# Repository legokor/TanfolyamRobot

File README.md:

# LEGO Kör - TanfolyamRobot

## Fejlesztő környezet

Korábban az STMicroelectronics által biztosított `STM32CubeIDE`-t használtuk a firmware fejlesztéséhez, azonban ez egy elég nehézkes és lassú eszköz. Ezért a tanfolyam során áttérünk egy könnyebben használható és gyorsabb parancssoros toolchain-re, az `STM32CubeCLT`-re. Ezt a toolchain-t a Visual Studio Code nevű (továbbiakban `VSCode`) kód szerkesztővel fogjuk használni, így a teljes fejlesztés (fordítás, feltöltés) nagyon könnyen indítható lesz néhány előre beállított `task`-kal.

## Toolchain

Az előző fejezetben említett módon a firmware fejlesztéséhez az STMicroelectronics parancsoros eszközeit használjuk. Sajnos ezek letöltése regisztrációhoz kötött, ezért feltöltöttük a telepítő fájlokat [a körös drive-ra](https://drive.google.com/drive/folders/1nJ2nfvr9kbIkVAWmcgEXpbxK1OUlX8sQ?usp=sharing), így regisztráció nélkül is telepíteni tudjátok - persze teljesen megértjük, ha nem akartok random drive-os fájlokat telepíteni, viszont ez esetben muszáj regisztrálnotok az [STMicroelectronics weboldalán](https://www.st.com/en/development-tools/stm32cubeclt.html), és onnan letölteni.

Letöltés után a telepítő fájlt futtatva telepítsétek a `STM32CubeCLT`-t egy kényelmes helyre, például `C:\STM32CubeCLT`-be.

**FONTOS:** az `STM32CubeCLT` telepítése után újra kell indítani a `VSCode`-ot amennyiben az már meg volt nyitva, különben a `VSCode` nem fogja látni a telepített toolchain-t. Ezen felül Linux rendszerek esetében előfordulhat, hogy a gépet is újra kell indítani, hogy a megfelelő környezeti változók beálljanak.

Jelenleg Windows 10/11-en és Ubuntu-n teszteljük a szoftvert. Más (Linux alapú) platformokon is valószínűleg működni fog - de ezt nem tudjuk garantálni.

## Robot illesztőszoftver

A robotra a firmware letöltése virtuális soros porton történik, a roboton az USB csatlakozó egy `FT232RL` chiphez kapcsolódik.

Előfordulhat Windows esetében, hogy az nem telepíti automatikusan a virtuális soros port driverét. Erre az esetre a fentebbi drive linken elérhető Windows zip-ben találtok egy plusz driver telepítőt, de amúgy ezt is le tudjátok tölteni az [FTDI weboldaláról](https://ftdichip.com/wp-content/uploads/2021/08/CDM212364_Setup.zip), majd pedig kibontani és telepíteni.

## Kiinduló projekt letöltése, megnyitása

A kiinduló projektet a [GitHub repojából](https://github.com/legokor/TanfolyamRobot) tudjuk letölteni, ehhez az oldal megnyitása után jobb oldalt a `Releases` fül alatt kell kiválasztanunk a **legújabb kiadást**, majd a `tanfrobot.zip` fájlra kell kattintani.

A letöltött fájlt helyezzük el egy kényelmes helyre, például `Documents/Lego_Tanfolyam` mappába, majd bontsuk ki. A kibontás után nyissuk meg a `VSCode`-ot, és a `File -> Open Folder...` menüponttal nyissuk meg a kibontott `firmware` mappát (mely többek közt az `Application`, `Drivers`, `Tools` könyvtárakat tartalmazza).

*Extra tipp:* a `VSCode`-ban érdemes telepíteni az `ms-vscode.cpptools` nevű bővítményt, mely C/C++ nyelv támogatást ad a szerkesztőhöz, így például szintaxis kiemelést és automatikus kiegészítést biztosít.

--------------------------------------------

--------------------------------------------

## *Csak a tanfolyamon kell:* projekt áttekintése, build és upload

Az imént megnyitott projektünk fájljait az IDE bal oldalán láthatjuk. A kód számunkra lényegi része a `tanfolyamrobot/Application/src/app.c` fájl lesz. Itt kell majd megoldanunk a tanfolyam során a feladatokat. Az itt található `app_main()` függvény gombnyomásra indul. Ha ebből a függvényből visszatér a programunk, akkor a robot leáll és a kijelzőn megjeleníti a visszatérési értéket.

A kód fordításához és a robotra való feltöltéséhez a `VSCode`-ban előre beállítottunk néhány `task`-ot, melyeket a `CTRL+SHIFT+B` billentyűkombinációval tudtok elindítani. E billentyűkombináció megnyomása után egy legördülő menüből választhatjátok ki, hogy mit szeretnétek csinálni - számunkra a `CMake Build` és az `STM32 Flash Firmware (FTDI)` lesz a fontos. Előbbi lefordítja a kódot, utóbbi pedig feltölti a robotra. A kiválasztás után egy újabb kérdés fog megjelenni, hogy melyik konfigurációt szeretnénk használni - válasszuk a `Release`-t, majd nyomjunk egy entert.

**FONTOS:** a `CMake Build`-et mindig futtassátok le a `STM32 Flash Firmware (FTDI)` előtt, különben a régi kód fog futni a roboton, nem pedig a legutóbb módosított verzió.

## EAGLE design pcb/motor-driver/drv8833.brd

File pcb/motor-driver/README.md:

# DRV8833 module

This is a carrier board for the DRV8833 dual H-bridge motor driver chip. It is a drop-in replacement for the cheap chinese 12 pin version.

Improvements:
 * Current sense resistors for the chip's current limiter feature
 * More capacitance on the power rail
 * Fault LED
 * Active-high fault output (still open-collector)

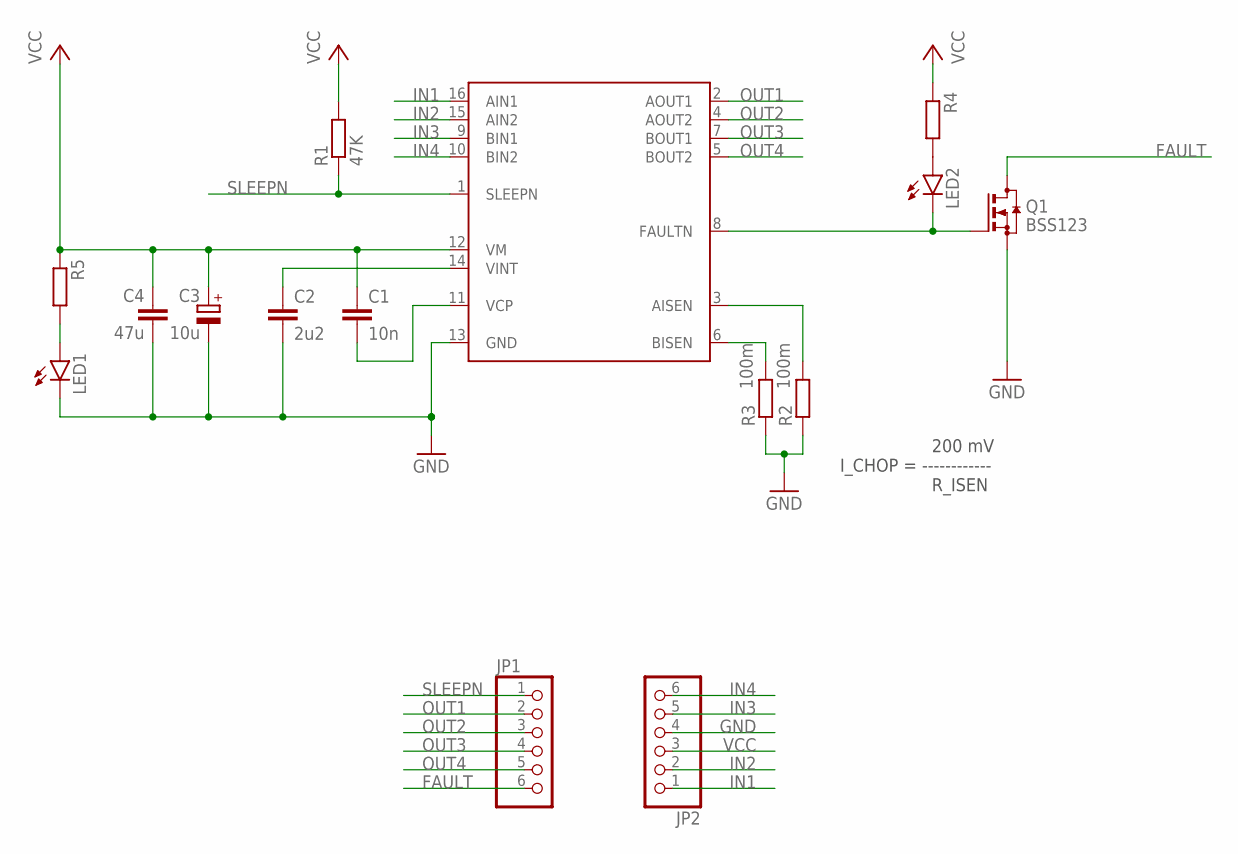
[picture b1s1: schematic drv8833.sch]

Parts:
C1: 10n; C0603
C2: 2u2; C0603
C3: 10u; A/3216-18W
C4: 47u; C1210
JP1, JP2: PINHD-1X6; 1X06
LED1, LED2: LEDCHIPLED_0805; CHIPLED_0805
Q1: BSS123; SOT23
R1: 47K; R0603
R2, R3: 100m; R1206
R4, R5: R0603
U$1: DRV8833; TSSOP-16

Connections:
AISEN: R2.2, U$1.3 (AISEN)
BISEN: R3.2, U$1.6 (BISEN)
FAULT: JP1.6, Q1.3 (D)
FAULTN: LED2.C, Q1.1 (G), U$1.8 (FAULTN)
FLT_AN: LED2.A, R4.2
GND: C2.2, C3.-, C4.2, JP2.4, LED1.C, Q1.2 (S), R2.1, R3.1, U$1.13 (GND)
IN1: JP2.1, U$1.16 (AIN1)
IN2: JP2.2, U$1.15 (AIN2)
IN3: JP2.5, U$1.9 (BIN1)
IN4: JP2.6, U$1.10 (BIN2)
OUT1: JP1.2, U$1.2 (AOUT1)
OUT2: JP1.3, U$1.4 (AOUT2)
OUT3: JP1.4, U$1.7 (BOUT1)
OUT4: JP1.5, U$1.5 (BOUT2)
PWR_LED: LED1.A, R5.2
SLEEPN: JP1.1, R1.1, U$1.1 (SLEEPN)
VCC: C1.1, C3.+, C4.1, JP2.3, R1.2, R4.1, R5.1, U$1.12 (VM)
VCP: C1.2, U$1.11 (VCP)
VINT: C2.1, U$1.14 (VINT)

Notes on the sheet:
200 mV I_CHOP = ------------ R_ISEN

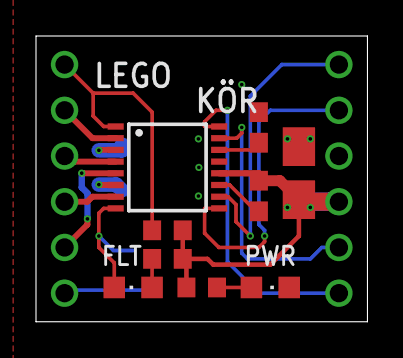
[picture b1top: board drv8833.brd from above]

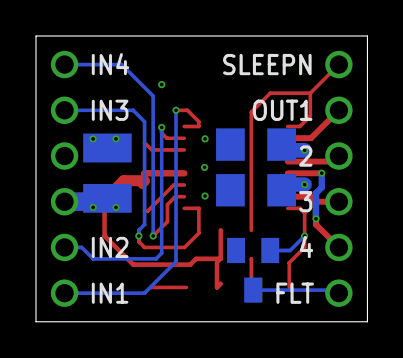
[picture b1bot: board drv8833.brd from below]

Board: 2 copper layers, 18.4 x 15.9 mm, 15 parts (6 on the bottom side), 19 nets.

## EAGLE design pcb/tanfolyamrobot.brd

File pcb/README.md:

# TanfolyamRobot - PCB design considerations

_Note: schematic net and pin names are formatted like_ `this`.

## Microcontroller

The main MCU is an [STM32F103C8T6](https://www.st.com/resource/en/datasheet/stm32f103c8.pdf) in LQFP64 package. There's an option to add an ESP8266 module which communicates with the main MCU via UART.

**The full STM32 pinout and pin assignments can be found in [STM32F103_pin_assignment.xls](STM32F103_pin_assignment.xls)**

### Programming

The STM32 can be programmed using the Serial Wire Debug interface or the integrated Device Firmware Updater. The F103's DFU only supports USART1, so that's connected to an FTDI FT232RL USB-UART converter.

In order to use the DFU, the MCU must be booted in System memory mode by pulling the `BOOT0` pin high at reset.
`BOOT0` is controlled by:
 * the FTDI chip's `RSTN` reset signal, which is high when USB is connected.
 * an FTDI output pin controlled by PC software. The pin can be selected by solder jumpers.

### Reset

Both controllers are connected to the same reset signal, which is a combination of the following reset sources:
 * The reset button
 * Debugger port
 * USB 5V connection
 * an FTDI output pin controlled by PC software. The pin can be selected by solder jumpers.

## Power supply

The battery input connects through a polarity protection MOSFET to the `VCC` rail, which drives the motors and the 5V regulator. Therefore the battery voltage must be at least 5V + the regulator's dropout voltage, and can be as high as the motors' and the motor driver's maximum operating voltage. The polarity protection MOSFET's absolute maximum V<sub>GS</sub> and V<sub>DS</sub> must be higher than the supply voltage.

The `+5V` rail powers the FTDI chip, LCD, ultrasonic sensor, motor encoders, and the servo motor. Therefore the ultrasonic sensor and motor encoder outputs shall be connected to a 5V tolerant MCU pin or level-shifted to 3.3V.

The `+3V3` rail powers the rest of the system: STM32, ESP, color sensor, and it's also the `VCCIO` supply of the FTDI chip.

## Motors

The two motors are driven by a DRV8833 module. For maximum flexibility all of its input ports shall be connected to PWM cabable MCU pins, preferably using the same timer. The driver indicates overcurrent/overheat faults on the `FAULTN` pin, and the whole module can be enabled/disabled by the `SLEEPN` pin.

The STM32's timers have a built-in encoder pulse counter module, which uses the CH1-CH2 channel pair. The motors' encoder pins therefore shall be connected to these timer channels.

The servo output has a 3 pin header with 5V supply and a PWM pin.

## Sensors, LCD

The TCS3200 color sensor has a frequency output. 2 config pins activate the RGB color filters, and 2 config pins set the output frequency scaling. The output pin should be connected to a timer of the MCU. The timer's frequency is not critical as the output full scale frequency can be configured between 12 and 600 kHz.

The generic ultrasonic sensor has a trigger and an echo pin. `ECHO` shall be connected to an interrupt-capable MCU pin.

The character LCD screen operates in 4 bit mode. In this configuration only the `D4`-`D7`, `EN` and `RST` pins are used. Contrast can be set by a trimmer potentiometer on the board. The backlight is also controlled by the MCU, but the control signal is pulled up, so it's on by default.

# MCU connection requirement summary

_I know this looks terrible, but it's my only workaround for GitHub's alternating row colors :disappointed:_

| Component     | Pin/Schematic net      | Type             | MCU requiurement                              |
|---------------|------------------------|------------------|-----------------------------------------------|
| DRV8833       | `IN1`, `IN2`           | PWM/fix input    | 1 PWM, 1 PWM/fix, same timer for all channels |
|||||
|               | `IN3`, `IN4`           | PWM/fix input    | 1 PWM, 1 PWM/fix, same timer for all channels |
|||||
|               | `SLEEPN`               | input            | -                                             |
|||||
|               | `FAULTN`               | output, OC       | -                                             |
|||||
| Encoder       | `ENC1_A`, `ENC1_B`     | output           | Timer CH1 - CH2                               |
|||||
|               | `ENC2_A`, `ENC2_B`     | output           | Timer CH1 - CH2                               |
|||||
| Servo         | `SERVO`                | PWM input        | Timer                                         |
|||||
| TCS3200       | `S0`-`S3`              | input            | -                                             |
|||||
|               | `OUT`                  | frequency output | Timer                                         |
|||||
| Generic US    | `TRIG`                 | input            | -                                             |
|||||
|               | `ECHO`                 | output           | Interrupt                                     |
|||||
| LCD           | `RST`,`EN`, `D4`-`D7`  | input            | -                                             |
|||||
|               | `BACKLIGHT`            | input            | Preferably PWM                                |
|||||
| ESP8266       | `RX`, `TX`             | UART             | Any UART                                      |
|||||
| SWD connector | `SWCLK`, `SWDIO`, `SWO`| Debug            | Corresponding debugger pins                   |
|||||
| FT232RL       | `RX`, `TX`             | UART             | UART1                                         |

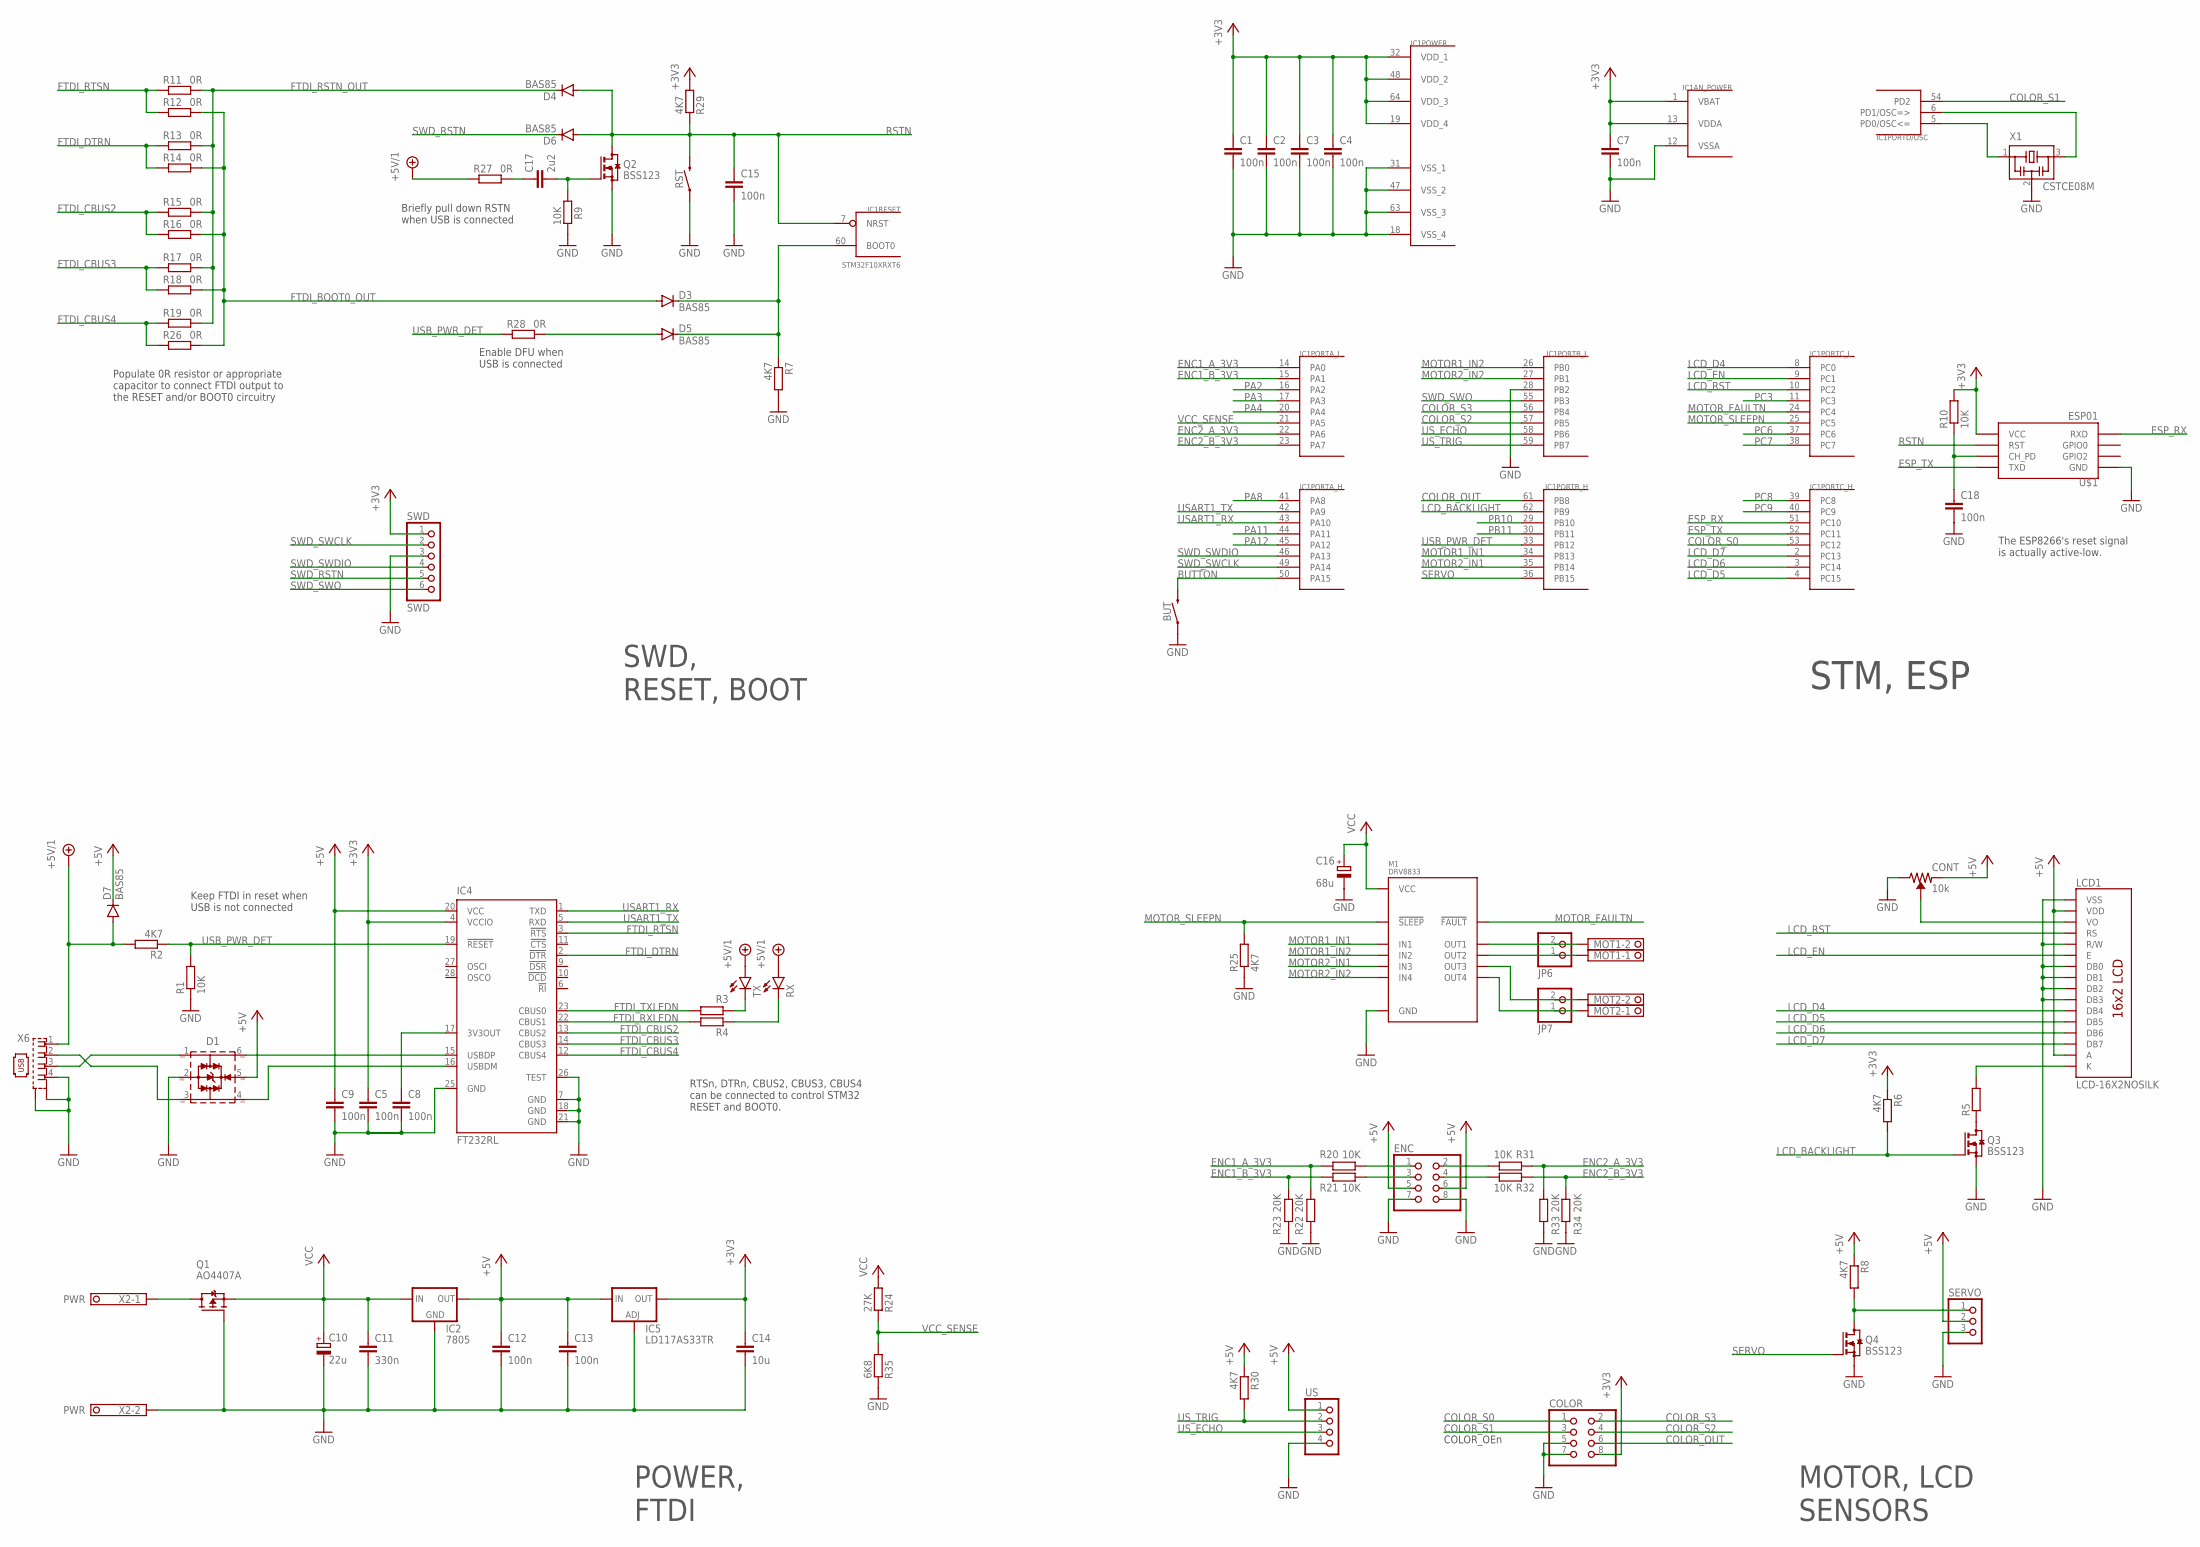
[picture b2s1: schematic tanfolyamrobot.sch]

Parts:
BUT: MOMENTARY-SWITCH-SPST-PTH-6.0MM; TACTILE_SWITCH_PTH_6.0MM
C1, C2, C3, C4, C5, C7, C8, C9, C15, C18: 100n; C0603
C10: 22u; B/3528-21R
C11: 330n; C0805K
C12, C13: 100n; C0805K
C14: 10u; C0805K
C16: 68u; B/3528-21R
C17: 2u2; C0603
COLOR: PINHD-2X4/90; 2X04/90
CONT: 10k; TRIMPOT-SMD-3MM-CLOSED
D1: 5Vdc; WE-TVS_SOT23-6L
D3, D4, D5, D6: BAS85; MICROMELF-W
D7: BAS85; DO-214AC
ENC: PINHD-2X4/90; 2X04/90
IC1: STM32F10XRXT6; TQFP64
IC2: 7805; DPACK
IC4: FT232RL; SSOP28
IC5: LD117AS33TR; SOT223
JP6, JP7: PINHD-1X2; 1X02
LCD1: LCD-16X2NOSILK; LCD-16X2_NOSILK
M1: DRV8833; DRV8833_MODULE
MOT1, MOT2: PWR; 1751248
Q1: AO4407A; SO-8
Q2, Q3, Q4: BSS123; SOT23
R1, R9, R10, R20, R21, R31, R32: 10K; R0603
R2, R6, R7, R8, R25, R29, R30: 4K7; R0603
R3, R4, R5: R-EU_R0603; R0603
R11, R12, R13, R14, R15, R16, R17, R18, R19, R26, R27, R28: 0R; R0603
R22, R23, R33, R34: 20K; R0603
R24: 27K; R0603
R35: 6K8; R0603
RST: MOMENTARY-SWITCH-SPST-PTH-6.0MM; TACTILE_SWITCH_PTH_6.0MM
RX: LEDCHIP-LED0603; CHIP-LED0603
SERVO: PINHD-1X3/90; 1X03/90
SWD: SWD; 1X06
TX: LEDCHIP-LED0603; CHIP-LED0603
U$1: ESP01
US: PINHD-1X4/90; 1X04/90
X1: CSTCE08M; CSTCE
X2: PWR; 1751248
X6: KUSBVX-BS1N

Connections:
3V3_FTDI: C8.1, IC4.17 (3V3OUT)
+3V3: C1.1, C2.1, C3.1, C4.1, C5.1, C7.1, C14.1, COLOR.8, IC1.1 (VBAT), IC1.13 (VDDA), IC1.19 (VDD_4), IC1.32 (VDD_1), IC1.48 (VDD_2), IC1.64 (VDD_3), IC4.4 (VCCIO), IC5.4 (OUT), R6.1, R10.2, R29.1, SWD.1, U$1.VCC
+5V: C9.1, C12.1, C13.1, CONT.1 (CCW), D1.5 (VDD), D7.C, ENC.5, ENC.6, IC2.3 (OUT), IC4.20 (VCC), IC5.3 (IN), LCD1.2 (VDD), LCD1.15 (A), R8.1, R30.1, SERVO.2, US.1
+5V/1: D7.A, R2.2, R27.1, RX.A, TX.A, X6.1
BOOT0: D3.C, D5.C, IC1.60 (BOOT0), R7.1
BUTTON: BUT.3 (2), IC1.50 (PA15)
COLOR_OUT: COLOR.6, IC1.61 (PB8)
COLOR_S0: COLOR.1, IC1.53 (PC12)
COLOR_S1: COLOR.3, IC1.54 (PD2)
COLOR_S2: COLOR.4, IC1.57 (PB5)
COLOR_S3: COLOR.2, IC1.56 (PB4)
ENC1_A_3V3: IC1.14 (PA0), R20.2, R22.1
ENC1_A_5V: ENC.1, R20.1
ENC1_B_3V3: IC1.15 (PA1), R21.2, R23.1
ENC1_B_5V: ENC.3, R21.1
ENC2_A_3V3: IC1.22 (PA6), R31.2, R33.1
ENC2_A_5V: ENC.2, R31.1
ENC2_B_3V3: IC1.23 (PA7), R32.2, R34.1
ENC2_B_5V: ENC.4, R32.1
ESP_CHPD: C18.1, R10.1, U$1.CH_PD
ESP_RX: IC1.51 (PC10), U$1.RX (RXD)
ESP_TX: IC1.52 (PC11), U$1.TX (TXD)
FTDI_BOOT0_OUT: D3.A, R12.2, R14.2, R16.2, R18.2, R26.2
FTDI_CBUS2: IC4.13 (CBUS2), R15.1, R16.1
FTDI_CBUS3: IC4.14 (CBUS3), R17.1, R18.1
FTDI_CBUS4: IC4.12 (CBUS4), R19.1, R26.1
FTDI_DTRN: IC4.2 (!DTR), R13.1, R14.1
FTDI_RSTN_OUT: D4.C, R11.2, R13.2, R15.2, R17.2, R19.2
FTDI_RTSN: IC4.3 (!RTS), R11.1, R12.1
FTDI_RXLEDN: IC4.22 (CBUS1), R4.2
FTDI_RXLEDN_R: R4.1, RX.C
FTDI_TXLEDN: IC4.23 (CBUS0), R3.2
FTDI_TXLEDN_R: R3.1, TX.C
GND: BUT.1, C1.2, C2.2, C3.2, C4.2, C5.2, C7.2, C8.2, C9.2, C10.-, C11.2, C12.2, C13.2, C14.2, C15.2, C16.-, C18.2, COLOR.5, COLOR.7, CONT.3 (CW), D1.2 (GND), ENC.7, ENC.8, IC1.12 (VSSA), IC1.18 (VSS_4), IC1.28 (PB2), IC1.31 (VSS_1), IC1.47 (VSS_2), IC1.63 (VSS_3), IC2.4 (GND), IC4.7 (GND), IC4.18 (GND), IC4.21 (GND), IC4.25 (GND), IC4.26 (TEST), IC5.1 (ADJ), LCD1.1 (VSS), LCD1.5 (R/W), LCD1.7 (DB0), LCD1.8 (DB1), LCD1.9 (DB2), LCD1.10 (DB3), M1.GND, Q1.4 (G), Q2.2 (S), Q3.2 (S), Q4.2 (S), R1.1, R7.2, R9.2, R22.2, R23.2, R25.1, R33.2, R34.2, R35.2, RST.1, SERVO.3, SWD.3, U$1.GND, US.4, X1.2, X2.2, X6.4, X6.M1 (S1), X6.M2 (S2)
LCD_BACKLIGHT: IC1.62 (PB9), Q3.1 (G), R6.2
LCD_CONTRAST: CONT.2 (WIPER), LCD1.3 (VO)
LCD_D4: IC1.8 (PC0), LCD1.11 (DB4)
LCD_D5: IC1.4 (PC15), LCD1.12 (DB5)
LCD_D6: IC1.3 (PC14), LCD1.13 (DB6)
LCD_D7: IC1.2 (PC13), LCD1.14 (DB7)
LCD_EN: IC1.9 (PC1), LCD1.6 (E)
LCD_K: LCD1.16 (K), R5.2
LCD_RST: IC1.10 (PC2), LCD1.4 (RS)
MOTOR1_IN1: IC1.34 (PB13), M1.IN1
MOTOR1_IN2: IC1.26 (PB0), M1.IN2
MOTOR2_IN1: IC1.35 (PB14), M1.IN3
MOTOR2_IN2: IC1.27 (PB1), M1.IN4
MOTOR_FAULTN: IC1.24 (PC4), M1.!FAULT
MOTOR_SLEEPN: IC1.25 (PC5), M1.!SLEEP, R25.2
unnamed: Q3.3 (D), R5.1
unnamed: C17.2, Q2.1 (G), R9.1
unnamed: Q1.5 (D), Q1.6 (D), Q1.7 (D), Q1.8 (D), X2.1
unnamed: C17.1, R27.2
unnamed: D5.A, R28.2
unnamed: JP6.2, M1.OUT1, MOT1.2
unnamed: JP6.1, M1.OUT2, MOT1.1
unnamed: JP7.2, M1.OUT3, MOT2.2
unnamed: JP7.1, M1.OUT4, MOT2.1
OSCIN: IC1.5 (PD0/OSC<=), X1.1
OSCOUT: IC1.6 (PD1/OSC=>), X1.3
PA2: IC1.16 (PA2)
PA3: IC1.17 (PA3)
PA4: IC1.20 (PA4)
PA8: IC1.41 (PA8)
PA11: IC1.44 (PA11)
PA12: IC1.45 (PA12)
PB10: IC1.29 (PB10)
PB11: IC1.30 (PB11)
PC3: IC1.11 (PC3)
PC6: IC1.37 (PC6)
PC7: IC1.38 (PC7)
PC8: IC1.39 (PC8)
PC9: IC1.40 (PC9)
RSTN: C15.1, D4.A, D6.A, IC1.7 (NRST), Q2.3 (D), R29.2, RST.3 (2), U$1.RST
SERVO: IC1.36 (PB15), Q4.1 (G)
SERVO_5V: Q4.3 (D), R8.2, SERVO.1
SWD_RSTN: D6.C, SWD.5
SWD_SWCLK: IC1.49 (PA14), SWD.2
SWD_SWDIO: IC1.46 (PA13), SWD.4
SWD_SWO: IC1.55 (PB3), SWD.6
USART1_RX: IC1.43 (PA10), IC4.1 (TXD)
USART1_TX: IC1.42 (PA9), IC4.5 (RXD)
USB_DM: D1.3 (I/O2), X6.2
USB_DM_FTDI: D1.4 (I/O4), IC4.16 (USBDM)
USB_DP: D1.1 (I/O1), X6.3
USB_DP_FTDI: D1.6 (I/O3), IC4.15 (USBDP)
USB_PWR_DET: IC1.33 (PB12), IC4.19 (!RESET), R1.2, R2.1, R28.1
US_ECHO: IC1.58 (PB6), US.3
US_TRIG: IC1.59 (PB7), R30.2, US.2
VCC: C10.+, C11.1, C16.+, IC2.1 (IN), M1.VCC, Q1.1 (S), Q1.2 (S), Q1.3 (S), R24.1
VCC_SENSE: IC1.21 (PA5), R24.2, R35.1

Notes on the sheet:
Keep FTDI in reset when USB is not connected
RTSn, DTRn, CBUS2, CBUS3, CBUS4 can be connected to control STM32 RESET and BOOT0.
STM, ESP
SWD, RESET, BOOT
MOTOR, LCD SENSORS
POWER, FTDI
COLOR_OEn
Briefly pull down RSTN when USB is connected
Enable DFU when USB is connected
Populate 0R resistor or appropriate capacitor to connect FTDI output to the RESET and/or BOOT0 circuitry
The ESP8266's reset signal is actually active-low.

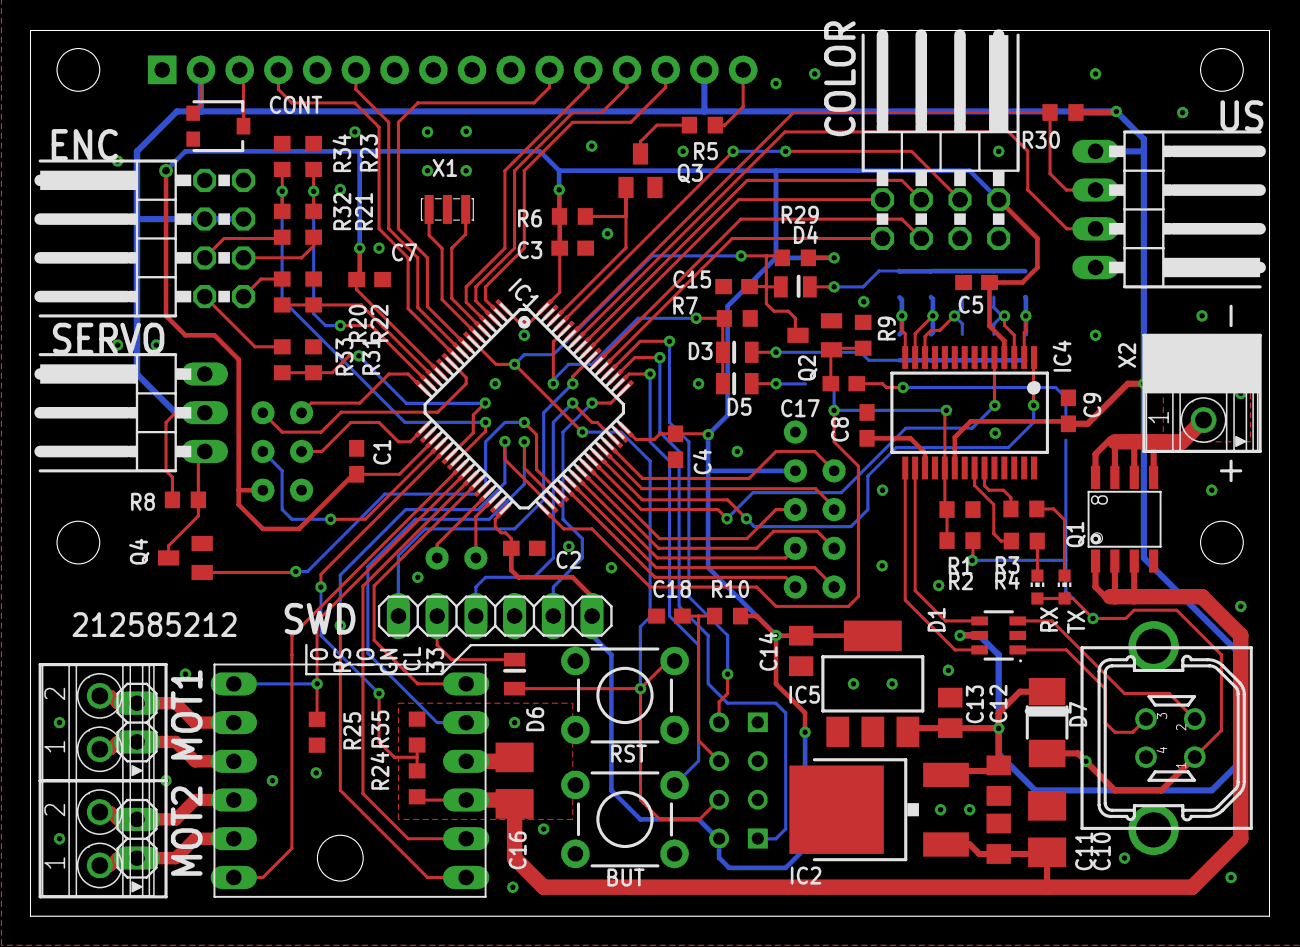
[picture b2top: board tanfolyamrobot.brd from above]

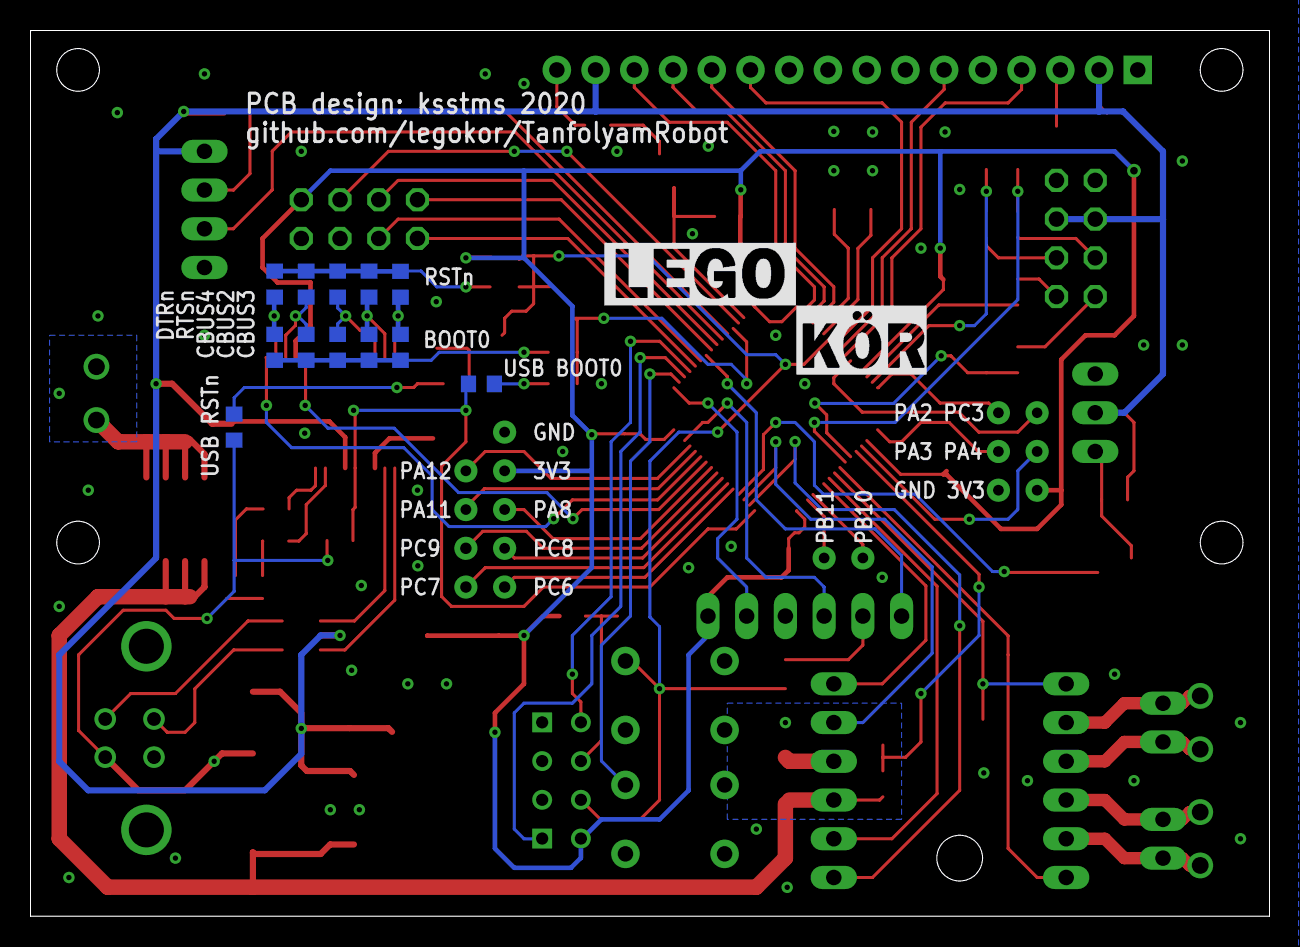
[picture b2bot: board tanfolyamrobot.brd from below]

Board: 2 copper layers, 81.3 x 58.1 mm, 86 parts (12 on the bottom side), 78 nets.

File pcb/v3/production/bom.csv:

Designator,Footprint,Quantity,Value,LCSC Part #
,,1,,
"BUT0, RST0",TACTILE_SWITCH_PTH_6.0MM,2,MOMENTARY-SWITCH-SPST-PTH-6.0MM,
"C1, C15, C18, C2, C3, C4, C5, C6, C7, C8, C9",C0603,11,100n,
C10,B_3528-21R,1,22u,
C11,C0805K,1,330n,
"C12, C13",C0805K,2,100n,
C14,C0805K,1,10u,
C16,B_3528-21R,1,68u,
C17,C0603,1,2u2,
"COLOR0, ENC0",2X04_90,2,PINHD-2X4/90,
CONT0,TRIMPOT-SMD-3MM-CLOSED,1,10k,
D1,WE-TVS_SOT23-6L,1,WE-TVS-HS_SOT23-6L_82400102,
"D3, D4, D6",MICROMELF-W,3,BAS85,
D7,DO-214AC,1,BAS85,
JP1,SolderJumper-2_P1.3mm_Open_Pad1.0x1.5mm,1,SolderJumper_2_Open,
"JP6, JP7",1X02,2,PINHD-1X2,
LCD1,LCD-16X2_NOSILK,1,LCD-16X2NOSILK,
M1,DRV8833_MODULE,1,DRV8833,
"MOT1, MOT2, X2",1751248,3,1751248,
Q1,SO-8,1,BSO201SP,
"Q2, Q3, Q4",SOT23,3,BSS123,
"R1, R10, R20, R21, R31, R32, R9",R0603,7,10K,
"R2, R25, R29, R30, R6, R7",R0603,6,4K7,
"R22, R23, R33, R34",R0603,4,20K,
R24,R0603,1,27K,
"R3, R4, R5",R0603,3,R-EU_R0603,
R35,R0603,1,6K8,
R8,R0603,1,330R,
"RX0, TX0",CHIP-LED0603,2,LEDCHIP-LED0603,
SERVO0,1X03_90,1,PINHD-1X3/90,
SW1,SW_E-Switch_EG1271_SPDT,1,SW_DPDT_x2,
SWD0,1X06,1,SWD,
U$1,ESP01,1,ESP01,
U1,LQFP-64_10x10mm_P0.5mm,1,STM32F411RCTx,
U2_2,DPACK,1,LP2950?CDT,
U2,PCB_IMU,1,~,
U4,SSOP28,1,FT232RL,
U5,SOT223,1,LD117A?S,
US0,1X04_90,1,PINHD-1X4/90,
X1,CSTCE,1,MURATA_CSTCE,
X6,KUSBVX-BS1N,1,KUSBVX-BS1N,

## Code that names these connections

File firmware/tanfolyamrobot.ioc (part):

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Mcu.Name=STM32F103R(8-B)Tx
Mcu.Package=LQFP64
Mcu.UserName=STM32F103R8Tx
PA0-WKUP.GPIOParameters=GPIO_Label,GPIO_ModeDefaultEXTI
PA0-WKUP.GPIO_Label=ENC1_A
PA0-WKUP.GPIO_ModeDefaultEXTI=GPIO_MODE_IT_RISING
PA0-WKUP.Signal=GPXTI0
PA1.GPIOParameters=GPIO_Label
PA1.GPIO_Label=ENC1_B
PA1.Signal=GPIO_Input
PA10.Mode=Asynchronous
PA10.Signal=USART1_RX
PA13.Mode=Trace_Asynchronous_SW
PA13.Signal=SYS_JTMS-SWDIO
PA14.Mode=Trace_Asynchronous_SW
PA14.Signal=SYS_JTCK-SWCLK
PA15.GPIOParameters=GPIO_PuPd,GPIO_Label
PA15.GPIO_Label=BUTTON
PA15.GPIO_PuPd=GPIO_PULLUP
PA15.Signal=GPIO_Input
PA2.GPIOParameters=GPIO_Label
PA2.GPIO_Label=SERVO
PA2.Signal=S_TIM2_CH3
PA5.GPIOParameters=GPIO_Label
PA5.GPIO_Label=VCC_SENSE
PA5.Signal=ADCx_IN5
PA6.GPIOParameters=GPIO_Label,GPIO_ModeDefaultEXTI
PA6.GPIO_Label=ENC2_A
PA6.GPIO_ModeDefaultEXTI=GPIO_MODE_IT_RISING
PA6.Signal=GPXTI6
PA7.GPIOParameters=GPIO_Label
PA7.GPIO_Label=ENC2_B
PA7.Signal=GPIO_Input
PA9.Mode=Asynchronous
PA9.Signal=USART1_TX
PB0.GPIOParameters=GPIO_Label
PB0.GPIO_Label=MOTOR1_PWM2
PB0.Signal=S_TIM3_CH3
PB1.GPIOParameters=GPIO_Label
PB1.GPIO_Label=MOTOR2_PWM2
PB1.Signal=S_TIM3_CH4
PB10.GPIOParameters=GPIO_Label,GPIO_Pu
PB10.GPIO_Label=IMU_SCL
PB10.GPIO_Pu=GPIO_PULLUP
PB10.Mode=I2C
PB10.Signal=I2C2_SCL
PB11.GPIOParameters=GPIO_Label,GPIO_Pu
PB11.GPIO_Label=IMU_SDA
PB11.GPIO_Pu=GPIO_PULLUP
PB11.Mode=I2C
PB11.Signal=I2C2_SDA
PB12.GPIOParameters=GPIO_PuPd,GPIO_Label
PB12.GPIO_Label=USB_PWR_DET
PB12.GPIO_PuPd=GPIO_PULLDOWN
PB12.Signal=GPIO_Input
PB13.GPIOParameters=GPIO_Label
PB13.GPIO_Label=MOTOR1_PWM1
PB13.Mode=PWM Generation1 CH1N
PB13.Signal=TIM1_CH1N
PB14.GPIOParameters=GPIO_Label
PB14.GPIO_Label=MOTOR2_PWM1
PB14.Mode=PWM Generation2 CH2N
PB14.Signal=TIM1_CH2N
PB3.Mode=Trace_Asynchronous_SW
PB3.Signal=SYS_JTDO-TRACESWO
PB4.GPIOParameters=GPIO_Label
PB4.GPIO_Label=COLOR_S3
PB4.Signal=GPIO_Output
PB5.GPIOParameters=GPIO_Label
PB5.GPIO_Label=COLOR_S2
PB5.Signal=GPIO_Output
PB6.GPIOParameters=GPIO_Label
PB6.GPIO_Label=TIM4_CH1_US_ECHO
PB6.Signal=S_TIM4_CH1
PB7.GPIOParameters=GPIO_Label,GPIO_ModeDefaultOutputPP
PB7.GPIO_Label=US_TRIG
PB7.GPIO_ModeDefaultOutputPP=GPIO_MODE_OUTPUT_OD
PB7.Signal=GPIO_Output
PB8.GPIOParameters=GPIO_Label
PB8.GPIO_Label=TIM4_CH3_COLOR
PB8.Signal=S_TIM4_CH3
PB9.GPIOParameters=PinState,GPIO_Label
PB9.GPIO_Label=LCD_BACKLIGHT
PB9.PinState=GPIO_PIN_RESET
PB9.Signal=GPIO_Output
PC0.GPIOParameters=GPIO_Label
PC0.GPIO_Label=LCD_D4
PC0.Signal=GPIO_Output
PC1.GPIOParameters=GPIO_Label
PC1.GPIO_Label=LCD_EN
PC1.Signal=GPIO_Output
PC10.Mode=Asynchronous
PC10.Signal=USART3_TX
PC11.Mode=Asynchronous
PC11.Signal=USART3_RX
PC12.GPIOParameters=GPIO_Label
PC12.GPIO_Label=COLOR_S0
PC12.Signal=GPIO_Output
PC13-TAMPER-RTC.GPIOParameters=GPIO_Label
PC13-TAMPER-RTC.GPIO_Label=LCD_D7
PC13-TAMPER-RTC.Signal=GPIO_Output
PC14-OSC32_IN.GPIOParameters=GPIO_Label
PC14-OSC32_IN.GPIO_Label=LCD_D6
PC14-OSC32_IN.Signal=GPIO_Output
PC15-OSC32_OUT.GPIOParameters=GPIO_Label
PC15-OSC32_OUT.GPIO_Label=LCD_D5
PC15-OSC32_OUT.Signal=GPIO_Output
PC2.GPIOParameters=GPIO_Label
PC2.GPIO_Label=LCD_RST
PC2.Signal=GPIO_Output
PC4.GPIOParameters=GPIO_PuPd,GPIO_Label
PC4.GPIO_Label=MOTOR_FAULTN
PC4.GPIO_PuPd=GPIO_PULLUP
PC4.Signal=GPIO_Input
PC5.GPIOParameters=PinState,GPIO_Label
PC5.GPIO_Label=MOTOR_SLEEPN
PC5.PinState=GPIO_PIN_RESET
PC5.Signal=GPIO_Output
PD0-OSC_IN.Mode=HSE-External-Oscillator
PD0-OSC_IN.Signal=RCC_OSC_IN
PD1-OSC_OUT.Mode=HSE-External-Oscillator
PD1-OSC_OUT.Signal=RCC_OSC_OUT
PD2.GPIOParameters=GPIO_Label
PD2.GPIO_Label=COLOR_S1
PD2.Signal=GPIO_Output
RCC.SYSCLKFreq_VALUE=72000000
RCC.SYSCLKSource=RCC_SYSCLKSOURCE_PLLCLK
board=custom

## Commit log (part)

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2020-08-31 refactored lcd driver, created a nicer wrapper for it (#7)
2020-09-09 fixed motor pwm pin name in configurator (#7)
2020-10-12 added launch config to gitignore
2020-10-15 changed the entire lcd lib to be interrupt-based (#7)
2020-10-15 integrated lcd lib (#7)
    Also had to change some timer settings in Cube.
    The IDE is now set to remove trailing spaces, so it created a ton of
    diffs. This should not occur in the future.
2020-10-17 added firmware update lib (#7)
2020-10-17 made firmware readme a tiny bit nicer
2020-10-17 added upload.sh (#7)
2020-10-17 enter dfu mode on uart message (#7)
2020-10-17 added upload script as external tool launch config (#7)
2020-10-17 chmod +x upload.sh
2020-10-20 fixed lcdClear return for real(#7)
    This was missing in 0ce3143
2020-10-20 fixed lcdClear return for real(#7)
    This was missing in dcf22ff
2020-10-21 added basic color sensor driver (#7)
2020-10-21 integrated color sensor driver (#7)
    This kinda breaks the lcd, because the timer interrupts occurs less
    frequently. The lcd handler should be moved to another timer.
2020-10-21 added missing volatile qualifier to uart variables (#7)
2020-11-02 disabled timer encoder mode, enabled interrupts on encoder pins (#7)
2020-11-02 added interrupt-based encoder driver (#7)
2020-11-02 integrated encoder driver (#7)
2020-11-03 enable float support in printf (#7)
2020-11-03 added ultrasonic sensor driver (#7)
2020-11-03 generated code for ultrasonic sensor input capture (#7)
2020-11-03 integrated ultrasonic sensor driver (#7)
2020-11-05 moved lcd to TIM2, some cosmetic changes (#7)
2020-11-05 configured pwm outputs (#7)
2020-11-05 added pwm and servo drivers (#7)
2020-11-05 added missing comments to pwm and servo libs (#7)
2020-11-05 added some more docs to firmware readme
2020-11-05 added description to the dfu code (#7)
2020-11-05 added battery voltage measurement (#7)
2020-11-05 changed servo signal pin pullup value (#1)
    The signal pin can draw some current, so a low resistance pullup is
    needed
2020-11-06 fixed lcd buffer concurrency problem (#7)
2020-11-13 added time measurement to upload script, increased baud rate
2020-11-13 added comments to the upload script
2020-11-14 added blocking data sending to lcd lib (#7)
2020-11-14 added custom character handling to the lcd lib (#7)
2020-11-15 convert adc measurement to battery voltage in irq handler (#7)
    also made it a bit nicer
2020-11-15 added battery indicator (#7)
2020-11-15 decreased splash screen duration
2020-11-15 added defines for peripherals, some cleanup (#7)
2020-11-16 fixed motor pwm pinout (#7)
    this was screwed up since 63c91f6
2020-11-16 added missing include paths for pwm and servo (#7)
    this is missing from ba90c89
2020-11-16 added missing include paths for pwm and servo (#7)
    this is missing from 6ab771f
2020-11-16 added motor lib (#7)
2020-11-17 reduced encoder resolution (#7)
    even this gives 0.375 degrees of wheel turn per encoder count
2020-11-17 changed encoder direction setting so it's like in the motor lib (#7)
2020-11-17 handle init failures (#7)
2020-11-20 fixed lcd error handling, some cleanup (#7)
2020-11-20 added upload script for windows
2020-11-20 moved linux upload script to tools
2020-11-20 added firmware upload description to firmware readme
2020-11-20 handle dfu requests in uart rx handler (#7)
    This way the mode switching delay doesn't depend on the main loop's
    duration.
    The USART1 IRQ preemption priority had to be lowered, so the LCD handler
    IRQs can interrupt the USART's handler.
2020-11-20 display battery indicator from timer irq handler (#7)
    For this the LCD cursor needs a setter and a getter, so the correct lcd
    state can be restored.
2020-11-20 don't allow half transfers in lcd buffer (#7)
2020-11-20 made battery characters const (#7)
2020-11-22 removed dfu request check from main loop (#7)
    This is missing from a85e733, but it causes no harm whatsoever.
2020-11-22 removed battery indicator display from main loop (#7)
    This is missing from 4f75615
2020-11-22 removed battery indicator display from main loop (#7)
    This is missing from 103985b
2020-11-23 modularized color sensor (#7)
2020-11-23 added application code, created some wrappers for robot control (#7)
2020-11-23 moved lcdPrintf to robotcontrol (#7)
    So the lcd driver doesn't have to include a bunch of std libraries
2021-02-07 fixed motor direction (#7)
2021-02-07 start user application after button is pressed (#7)
2021-02-08 added simulink stuff for motor controller tuning (#8)
2021-02-08 documented motor pid controller matlab stuff (#8)
2021-02-15 added connector pinouts
2021-02-15 added pinouts to README.md
2021-09-06 firmware for motor speed controller tuning (#8)
    This is some dirty stuff. Sorry.
2021-09-17 clear lcd before calling user application (#7)
2021-09-20 added calibration and hsv conversion to color sensor driver (#7)
2021-10-05 cube config change (#7)
    - increased motor pwm frequency
    - decreased lcd frequency
    - set servo output to simple gpio
2021-10-05 implemented motor speed controller (#8)
2021-10-05 added motor speed control to api (#8)
2021-10-10 fixed lcd comment (#7)
2021-10-10 added soft servo lib (#7)
2021-10-10 error if the application wants to use a non-existent motor (#7)
2021-10-10 add encoder to robotcontrol api (#7)
2021-10-10 include linux version of stm32flash
2021-10-11 pcb readme title fix
2021-10-11 started main readme
2021-10-11 check for division by 0 in color sensor lib (#7)
2021-10-11 started dev docs
2021-10-11 user readme
2021-10-11 typo fix
2021-10-12 return from default application insted of waiting in infinite loop (#7)
2021-10-12 Update robotcontrol.h
    fix motor names
2021-10-12 fixed motor names for real
2021-10-17 moved api functions to a separate header (#7)
2021-10-18 soft-pwm controlled lcd backlight (#7)
2021-10-18 added nullptr-checks to pwm and servo init functions (#7)
2021-10-18 typo fix in servo driver (#7)
2021-10-19 fix ultrasonic sensor pointer issue (#7)
    The instance of the sensor is also named "us" in main.c, so somehow it
    got mixed up with the pointer in robotcontrol.c
2021-10-19 changed servo signal pin to gpio (#7)
2021-10-19 typo fix in comment (#7)
2021-10-19 refactored soft-servo to use soft-pwm (#7)
2021-10-19 make sure to keep soft-pwm internal state correct (#7)
2021-10-19 disable servo for now (#7)
2021-10-19 reduced backlight intensity (#7)
2021-10-19 added timeout to ultrasonic measure (#7)
2021-10-19 fixed irq priorities (#7)
2021-10-24 don't create softpwm instance in softservo lib (#7)
2021-10-24 refactored soft-pwm lib (#7)
    Use the output compare function of a timer to generate delays between
    PWM signal edges. This should be much more efficient than the previous
    implementation, but it's less versatile and needs a timer channel for
    each instance.
2021-10-24 integrated the new soft-pwm and soft-servo libs (#7)
2021-10-26 add inversion option to soft-pwm, invert servo output (#7)
2021-10-26 added serial port stuff to main readme
2021-11-09 debugger documentation
2022-01-10 moved main pcb to separate directory
2022-01-10 added drv8833 module pcb (#10)
2022-03-10 added device manager screenshot
2022-03-10 fixed serial port stuff in main readme
2022-03-23 reduced photo sizes
2022-08-16 added lcd contrast setting to docs
2023-02-13 US sensor uninitialized variable fix
2023-02-13 new improved upload method
2023-02-14 run config file added
2023-02-16 Recalibrated color sensor
2023-02-16 vbat indicator calibration
2023-02-17 Move rgb to hsv conversion to separate function
2023-02-17 Add comment about the actual range used in HSV struct
2023-02-18 Changed distance measurement to non-blocking, measurement happens in the background
2023-02-19 low speed motor oscillation fixed by removing encoder rolling average
2023-02-21 rgb2hsv fix
2023-02-28 Servo bringup #19, encoder and lcd timer changed to TIM1
2023-03-14 test_app removed from build path
2023-04-07 first controller design for H_W model
2023-04-07 Move MATLAB files and update readme
2023-04-10 Updated motor control readme with wheel to shaft ratio
2023-04-11 Convert measurements to rad per sec from tick per sec
2023-05-02 uart send circular buffer added, baudrate increased to 1Mb/s, motor switched to brake_mode
2023-05-02 uart send circular buffer added, baudrate increased to 1Mb/s, motor switched to brake_mode 2
2023-06-17 environment settings fix
2023-06-17 motor id p1
2023-06-17 uart fix
2023-06-17 motor identification software V1.0
2023-06-17 encoder bug fix
2023-07-04 data format changed
2023-07-04 launch config fix
2023-07-22 gitignore for LICENSE.txt
2023-08-08 uart müxik xd
2023-08-08 App for remote control added
2023-10-09 first version of ESP uploader tool
2023-11-23 Added STM side UART communication for wireless debug interface
2023-11-23 language settings added to gitignore
2024-01-14 Started development of esp side comms
2024-01-16 Encoder, ESP and speedcontrol bug fixes
2024-01-18 added script for receiving serial telemetrics from stm
2024-01-18 ESP telemetry integration started
2024-01-18 fixup! ESP telemetry integration started
2024-01-18 Add server functionality to handle POST requests
2024-01-18 ESP integration: buggy ESPscanf
2024-02-05 added esp configuration through stm
2024-02-05 MŰKÖDIK A TELEMETRIA, NE NYÚLJ HOZZÁ
2024-02-08 telemetry software and start script added
2024-02-11 Telemetry bug fixes, upload config update
2024-02-12 Log component console added
2024-02-15 initial esp printf
2024-02-17 Auto server IP setter script
2024-02-18 ESP code fixes, refactoring and state indicator
2024-02-18 ESP bug fix and console cosmetics
2024-02-20 ESP bug fixes, IMU UI deactivated
2024-02-21 Release prep
2024-02-22 Function docs and encoder pos fix
2024-02-22 config fixes
2024-02-22 Docs updated
2024-02-22 Uploader .dll added
2024-05-13 Implemented IR sensor driver with conditional building.
2024-06-08 New PCB
    Added new version of pcb
2024-07-02 Single server for multiple colors
2024-07-02 frontend build
2024-07-02 fixup! frontend build
2024-07-06 .gitignore fix
2024-07-10 Included project file
2024-07-17 IMU integration into firmware and telemetry
2024-07-17 IMU orientation added to robot API
2025-01-31 major project and code restructuring and refactoring
2025-02-01 clock frequency changed to 72MHz
2025-02-01 delayUs impl added and precise right angle turn example
2025-02-05 ESP binary comm
2025-02-05 Multi color server and client first version
2025-02-05 service created
2025-02-05 IMU display added
2025-02-05 fixup! service created
2025-02-05 poster test script added
2025-02-05 telemetry dir path fix
2025-02-05 fixup! telemetry dir path fix
2025-02-05 build folder removed and other fixes
2025-02-05 Added raspberry pi setup shell script
2025-02-05 Update tanfrobot-telemetry.service user
2025-02-05 \n fix
2025-02-06 ip_setter removed and fixes
2025-02-06 esp firmware file renamed
2025-02-08 FTDI uploader project converted to CMake, Linux support added
2025-02-08 fixup! FTDI uploader project converted to CMake, Linux support added
2025-02-08 IOC file CubeMX version upgrade
2025-02-08 better ftdi_uploader error handling
2025-02-08 minor fixes, motor PID moved to period IT, TIM3 CH1 OC removed
2025-02-08 telemetry update rate reduced
2025-02-11 toolchain migration
2025-02-11 feat: add udev setup
2025-02-11 feat: linux suport
2025-02-11 fix: port auto selection
2025-02-11 boot mode exit fix
2025-02-13 test code final version
2025-02-13 getTimeMs impl
2025-02-13 final test code, getTimeMs added, delayUs change
2025-02-18 minor fixes
2025-02-18 feat: rebuild linux uploader
2025-02-18 minor robot API update
2025-02-18 new user guide added
2025-02-19 final README
2025-02-19 esp status fix
2025-02-20 readme clarification
2025-03-09 Rev1
2025-03-10 IMU init fix
2025-03-11 Fixed issues on schematic
2025-03-11 Fixed DRC
2025-03-23 Finishing touches
2025-08-12 Known issues and fixes
2026-02-22 setup vscode dev env
2026-02-23 make build linux friendly
2026-02-23 fix windows gcc paths
2026-02-23 fix minor issues and update docs
2026-02-24 Fix toolchain paths and update README

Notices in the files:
parts and their libraries:
SparkFun-Displays: Licensing: Creative Commons ShareAlike 4.0 International - https://creativecommons.org/licenses/by-sa/4.0
Wurth_EMC Components_WE-TVS: Copyright: Würth Elektronik
